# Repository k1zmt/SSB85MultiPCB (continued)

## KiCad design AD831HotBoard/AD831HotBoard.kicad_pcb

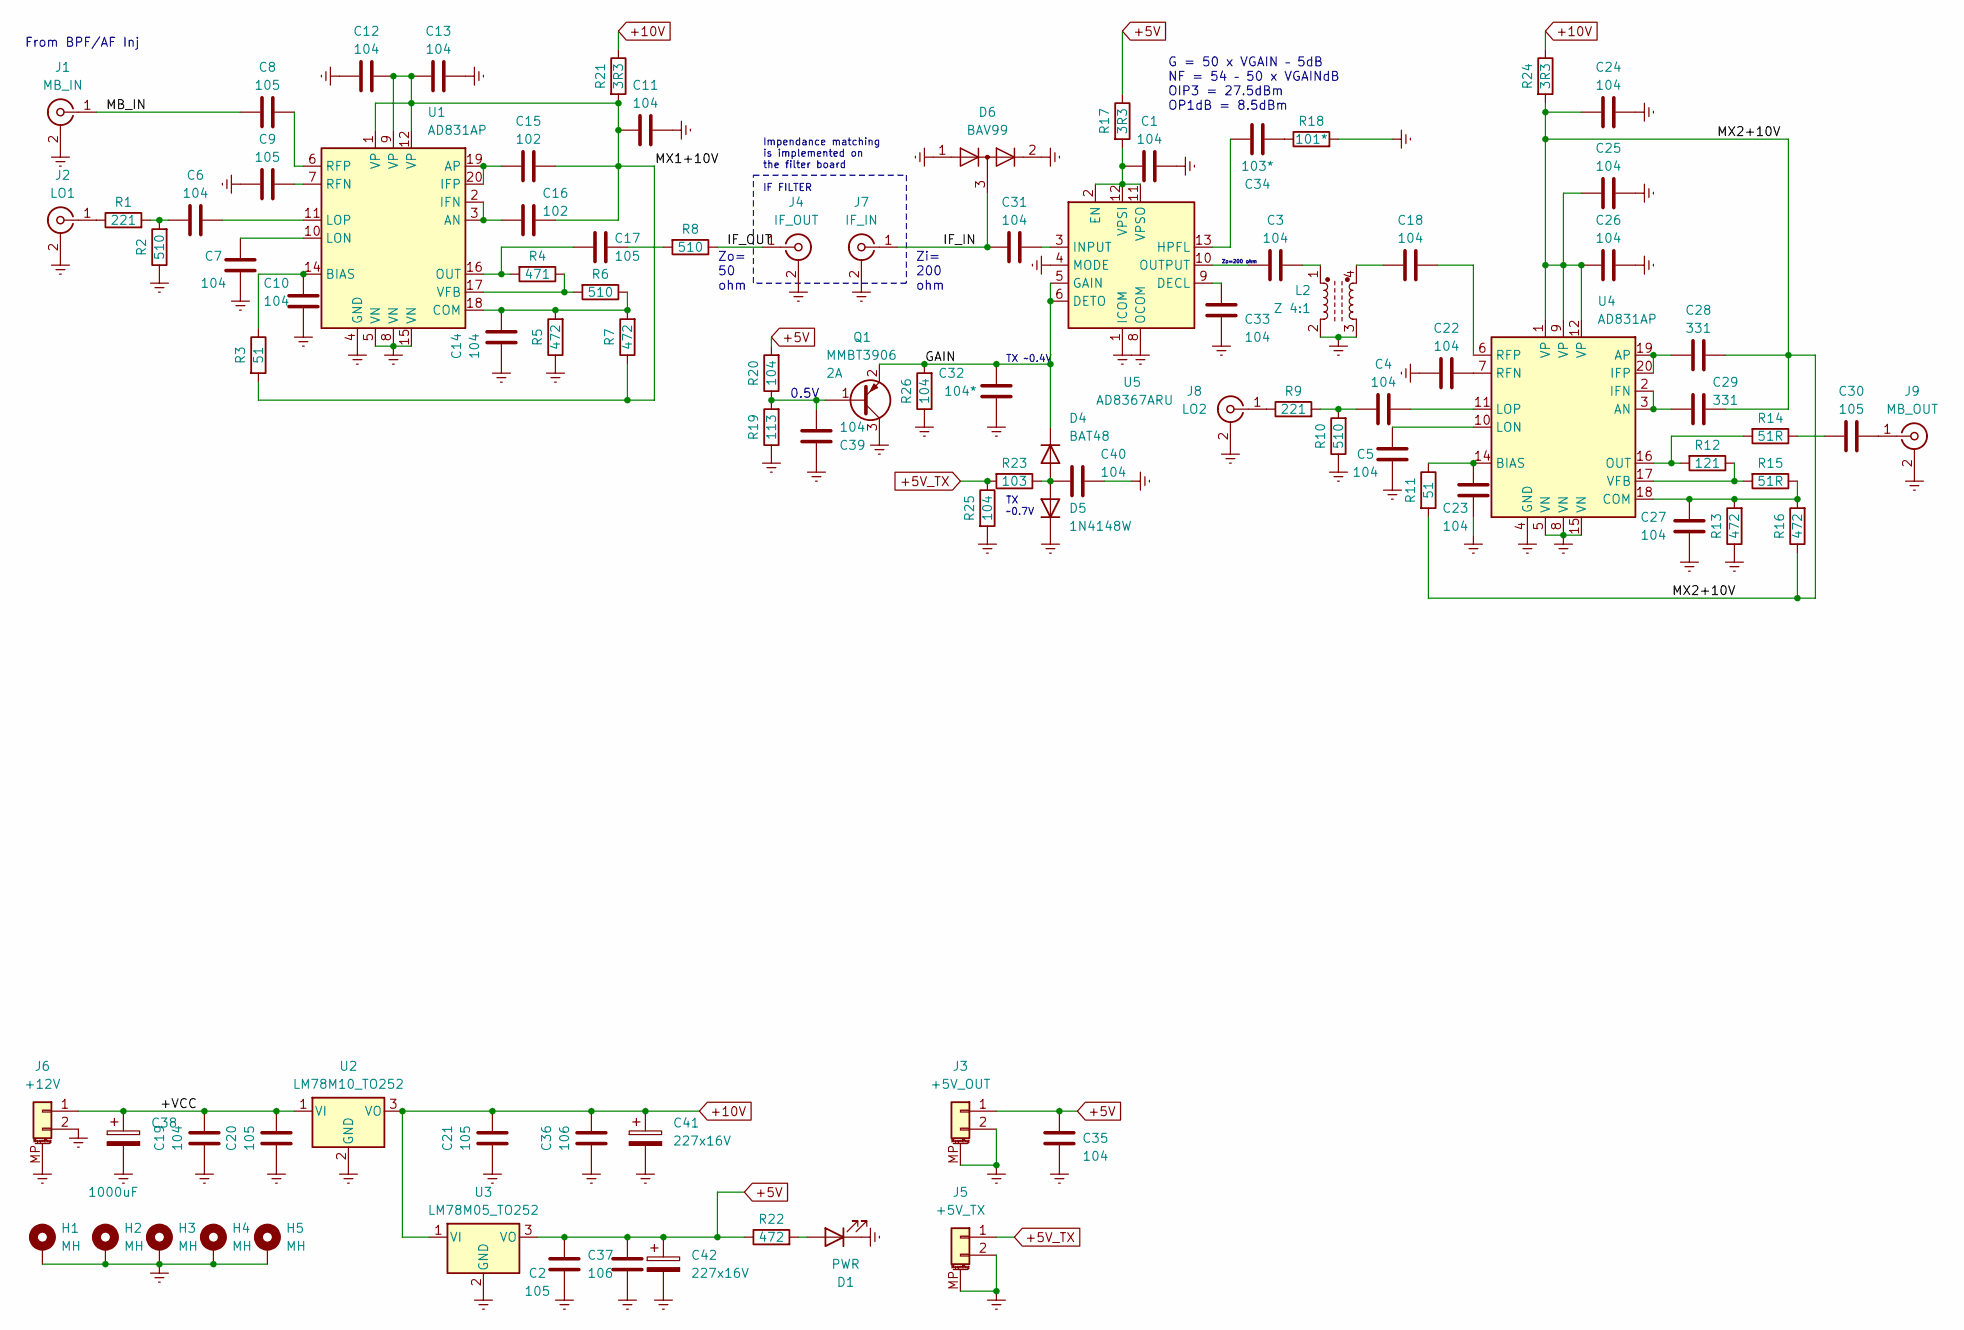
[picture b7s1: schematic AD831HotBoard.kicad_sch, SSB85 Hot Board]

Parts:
C1, C3, C4, C5, C6, C7, C10, C11, C12, C13, C14, C18, C19, C22, C23, C24, C25, C26, C27, C31, C33, C35, C39, C40: 104; C_0805_2012Metric
C2, C8, C9, C17, C21: 105; C_0805_2012Metric
C15, C16: 102; C_0805_2012Metric
C20: 105; C_1210_3225Metric
C28, C29: 331; C_0805_2012Metric
C30: 105; C_1206_3216Metric
C32: 104*; C_0805_2012Metric
C34: 103*; C_0805_2012Metric
C36, C37: 106; C_0805_2012Metric
C38: 1000uF; CP_Elec_10x12.5
C41, C42: 227x16V
D1: PWR; LED_0603_1608Metric
D4: BAT48; D_SOD-123
D5: 1N4148W; D_SOD-123
D6: BAV99; SOT-23
H1, H2, H3, H4, H5: MH; MountingHole_3.2mm_M3_Pad
J1: MB_IN; SMA_Samtec_SMA-J-P-X-ST-EM1_EdgeMount
J2: LO1; SMA_Samtec_SMA-J-P-X-ST-EM1_EdgeMount
J3: +5V_OUT; JST_PH_S2B-PH-SM4-TB_1x02-1MP_P2.00mm_Horizontal
J4: IF_OUT; SMA_Samtec_SMA-J-P-X-ST-EM1_EdgeMount
J5: +5V_TX; JST_PH_S2B-PH-SM4-TB_1x02-1MP_P2.00mm_Horizontal
J6: +12V; JST_PH_S2B-PH-SM4-TB_1x02-1MP_P2.00mm_Horizontal
J7: IF_IN; SMA_Samtec_SMA-J-P-X-ST-EM1_EdgeMount
J8: LO2; SMA_Samtec_SMA-J-P-X-ST-EM1_EdgeMount
J9: MB_OUT; SMA_Samtec_SMA-J-P-X-ST-EM1_EdgeMount
L2: Z 4:1; L_CommonModeChoke_Wuerth_WE-SL5
Q1: MMBT3906; SOT-23
R1, R9: 221; R_1206_3216Metric
R2, R6, R10: 510; R_0805_2012Metric
R3, R11: 51; R_0805_2012Metric
R4: 471; R_0805_2012Metric
R5, R7, R13, R16, R22: 472; R_0805_2012Metric
R8: 510; R_1206_3216Metric
R12: 121; R_0805_2012Metric
R14, R15: 51R; R_0805_2012Metric
R17, R21, R24: 3R3; R_1206_3216Metric
R18: 101*; R_0805_2012Metric
R19: 113; R_0805_2012Metric
R20, R25, R26: 104; R_0805_2012Metric
R23: 103; R_0805_2012Metric
U1, U4: AD831AP; PLCC-20
U2: LM78M10_TO252; TO-252-2
U3: LM78M05_TO252; TO-252-2
U5: AD8367ARU; TSSOP-14_4.4x5mm_P0.65mm

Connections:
+5V: C2.1, C35.1, C37.1, J3.1, R17.1, R20.2, R22.1, U3.3 (VO)
+5V_TX: J5.1, R23.2, R25.1
+10V: C21.1, C36.1, R21.1, R24.1, U2.3 (VO), U3.1 (VI)
/+VCC: C19.1, C20.1, C38.1, J6.1, U2.1 (VI)
/MX1+10V: C11.2, C12.2, C13.2, C15.1, C16.1, R3.2, R7.1, R21.2, U1.1 (VP), U1.9 (VP), U1.12 (VP)
/MX2+10V: C24.2, C25.2, C26.2, C28.1, C29.1, R11.2, R16.1, R24.2, U4.1 (VP), U4.9 (VP), U4.12 (VP)
Earth: C1.1, C2.2, C5.2, C7.2, C9.2, C10.2, C11.1, C12.1, C13.1, C14.2, C19.2, C20.2, C21.2, C22.2, C23.2, C24.1, C25.1, C26.1, C27.2, C32.2, C33.2, C35.2, C36.2, C37.2, C38.2, C39.2, C40.1, D1.1 (K), D5.1 (K), H1.1, H2.1, H3.1, H4.1, H5.1, J1.2 (Ext), J2.2 (Ext), J3.2, J3.MP (MountPin), J4.2 (Ext), J5.2, J5.MP (MountPin), J6.2, J6.MP (MountPin), J7.2 (Ext), J8.2 (Ext), J9.2 (Ext), L2.2, L2.3, Q1.3 (C), R2.1, R5.1, R10.1, R13.1, R18.2, R19.1, R25.2, U1.4 (GND), U1.5 (VN), U1.8 (VN), U1.13 (GND), U1.15 (VN), U2.2 (GND), U3.2 (GND), U4.4 (GND), U4.5 (VN), U4.8 (VN), U4.13 (GND), U4.15 (VN), U5.1 (ICOM), U5.4 (MODE), U5.7 (ICOM), U5.8 (OCOM), U5.14 (ICOM); also elsewhere on the board
unnamed: C3.1, L2.1
unnamed: C4.1, R9.2, R10.2
unnamed: C17.1, R8.2
unnamed: C18.2, L2.4
unnamed: C30.2, R14.1
unnamed: C34.2, R18.1
unnamed: D1.2 (A), R22.2
unnamed: C40.2, D4.2 (A), D5.2 (A), R23.1
unnamed: C8.2, J1.1 (In)
unnamed: J2.1 (In), R1.1
unnamed: J4.1 (In), R8.1
unnamed: J8.1 (In), R9.1
unnamed: C30.1, J9.1 (In)
unnamed: C39.1, Q1.1 (B), R19.2, R20.1
unnamed: C16.2, U1.2 (IFN), U1.3 (AN)
unnamed: C15.2, U1.19 (AP), U1.20 (IFP)
unnamed: C10.1, R3.1, U1.14 (BIAS)
unnamed: C14.1, R5.2, R6.1, R7.2, U1.18 (COM)
unnamed: C7.1, U1.10 (LON)
unnamed: C6.2, U1.11 (LOP)
unnamed: C17.2, R4.2, U1.16 (OUT)
unnamed: C9.1, U1.7 (RFN)
unnamed: C8.1, U1.6 (RFP)
unnamed: R4.1, R6.2, U1.17 (VFB)
unnamed: C29.2, U4.2 (IFN), U4.3 (AN)
unnamed: C28.2, U4.19 (AP), U4.20 (IFP)
unnamed: C23.1, R11.1, U4.14 (BIAS)
unnamed: C27.1, R13.2, R15.1, R16.2, U4.18 (COM)
unnamed: C5.1, U4.10 (LON)
unnamed: C4.2, U4.11 (LOP)
unnamed: R12.2, R14.2, U4.16 (OUT)
unnamed: C22.1, U4.7 (RFN)
unnamed: C18.1, U4.6 (RFP)
unnamed: R12.1, R15.2, U4.17 (VFB)
unnamed: C33.1, U5.9 (DECL)
unnamed: C1.2, R17.2, U5.2 (EN), U5.11 (VPSO), U5.12 (VPSI)
unnamed: C34.1, U5.13 (HPFL)
unnamed: C31.1, U5.3 (INPUT)
unnamed: C3.2, U5.10 (OUTPUT)

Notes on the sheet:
Zo= 50 ohm
Impendance matching is implemented on the filter board IF FILTER
G = 50 x VGAIN – 5dB NF = 54 – 50 x VGAINdB OIP3 = 27.5dBm OP1dB = 8.5dBm
From BPF/AF Inj
TX ~0.7V
Zo=200 ohm
TX ~0.4V
Zi= 200 ohm
0.5V

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
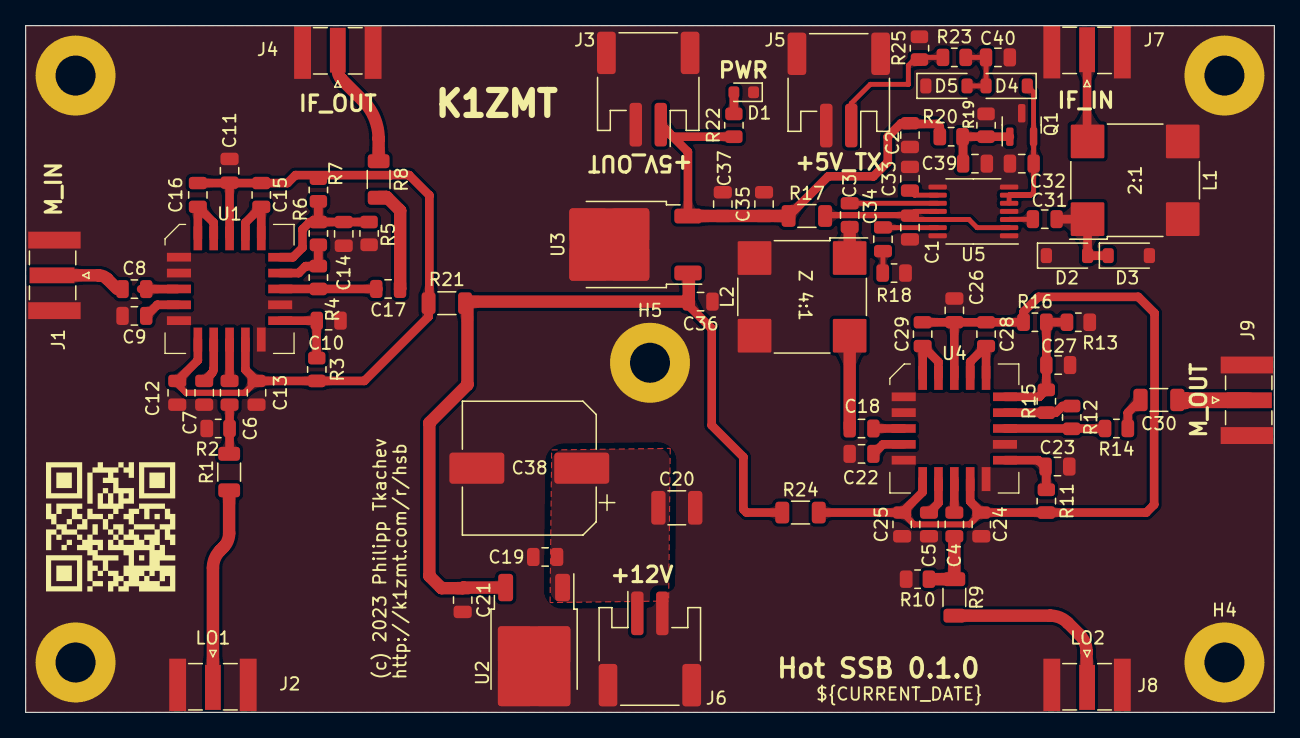
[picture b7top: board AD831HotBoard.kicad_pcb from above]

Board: 2 copper layers, 100.0 x 55.0 mm, 92 parts (0 on the bottom side), 50 nets.

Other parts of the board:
D2, D3: 1N4148W; D_SOD-123
L1: 2:1; L_CommonModeChoke_Wuerth_WE-SL5

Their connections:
Earth: D2.1 (K), D3.2 (A), L1.2, L1.3; also elsewhere on the board

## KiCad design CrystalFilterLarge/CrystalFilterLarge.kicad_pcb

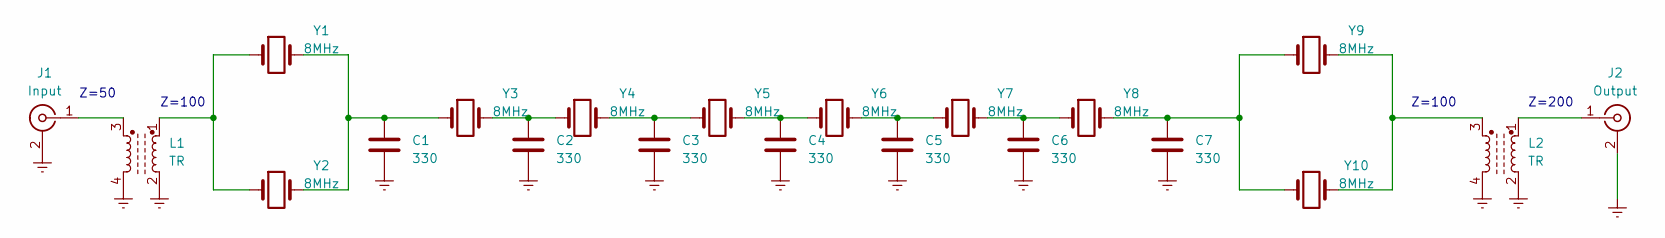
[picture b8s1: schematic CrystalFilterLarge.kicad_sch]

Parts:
C1, C2, C3, C4, C5, C6, C7: 330; C_0805_2012Metric
J1: Input; SMA_Samtec_SMA-J-P-X-ST-EM1_EdgeMount
J2: Output; SMA_Samtec_SMA-J-P-X-ST-EM1_EdgeMount
L1, L2: TR; Transformer_T37_W10_P5mm_1
Y1, Y2, Y3, Y4, Y5, Y6, Y7, Y8, Y9, Y10: 8MHz; Crystal_HC49-US_Vertical

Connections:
Earth: C1.1, C2.1, C3.1, C4.1, C5.1, C6.1, C7.1, J1.2 (Ext), J2.2 (Ext), L1.2, L1.4, L2.2, L2.4
unnamed: C1.2, Y1.2, Y2.2, Y3.1
unnamed: C2.2, Y3.2, Y4.1
unnamed: C3.2, Y4.2, Y5.1
unnamed: C4.2, Y5.2, Y6.1
unnamed: C5.2, Y6.2, Y7.1
unnamed: C6.2, Y7.2, Y8.1
unnamed: C7.2, Y8.2, Y9.1, Y10.1
unnamed: J1.1 (In), L1.3
unnamed: J2.1 (In), L2.1
unnamed: L1.1, Y1.1, Y2.1
unnamed: L2.3, Y9.2, Y10.2

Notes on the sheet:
Z=50
Z=100
Z=200

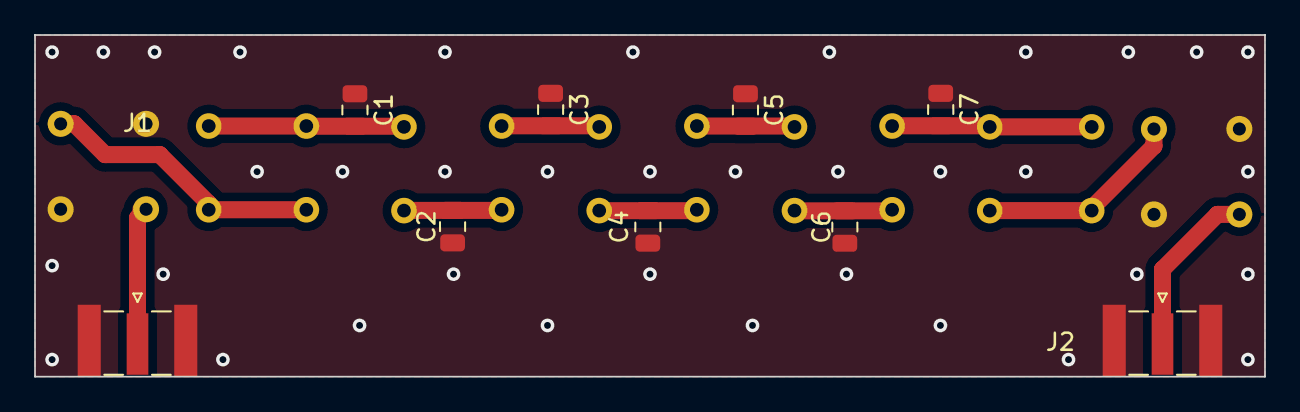
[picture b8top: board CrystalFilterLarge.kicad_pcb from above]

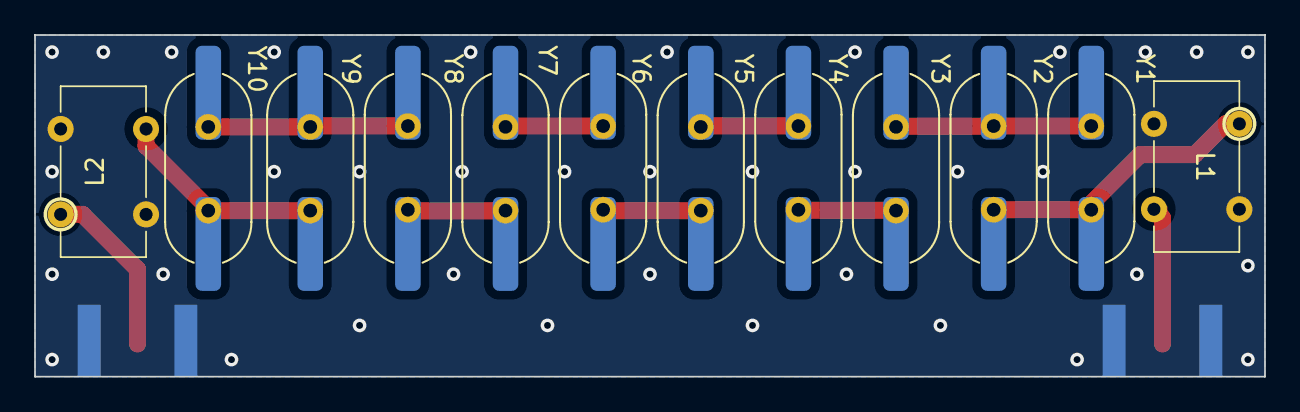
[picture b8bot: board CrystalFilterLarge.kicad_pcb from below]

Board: 2 copper layers, 72.0 x 20.0 mm, 21 parts (12 on the bottom side), 12 nets.
